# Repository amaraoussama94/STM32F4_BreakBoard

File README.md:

# STM32F4_BreakBoard
-KICad 5 Project
-MCU STM32F405RGT6
-4 layer PCB
-16MHz HSE 
-Power Regulator 
-SW For MCU
-LED For Test 
-SPI USARt I2C Bus

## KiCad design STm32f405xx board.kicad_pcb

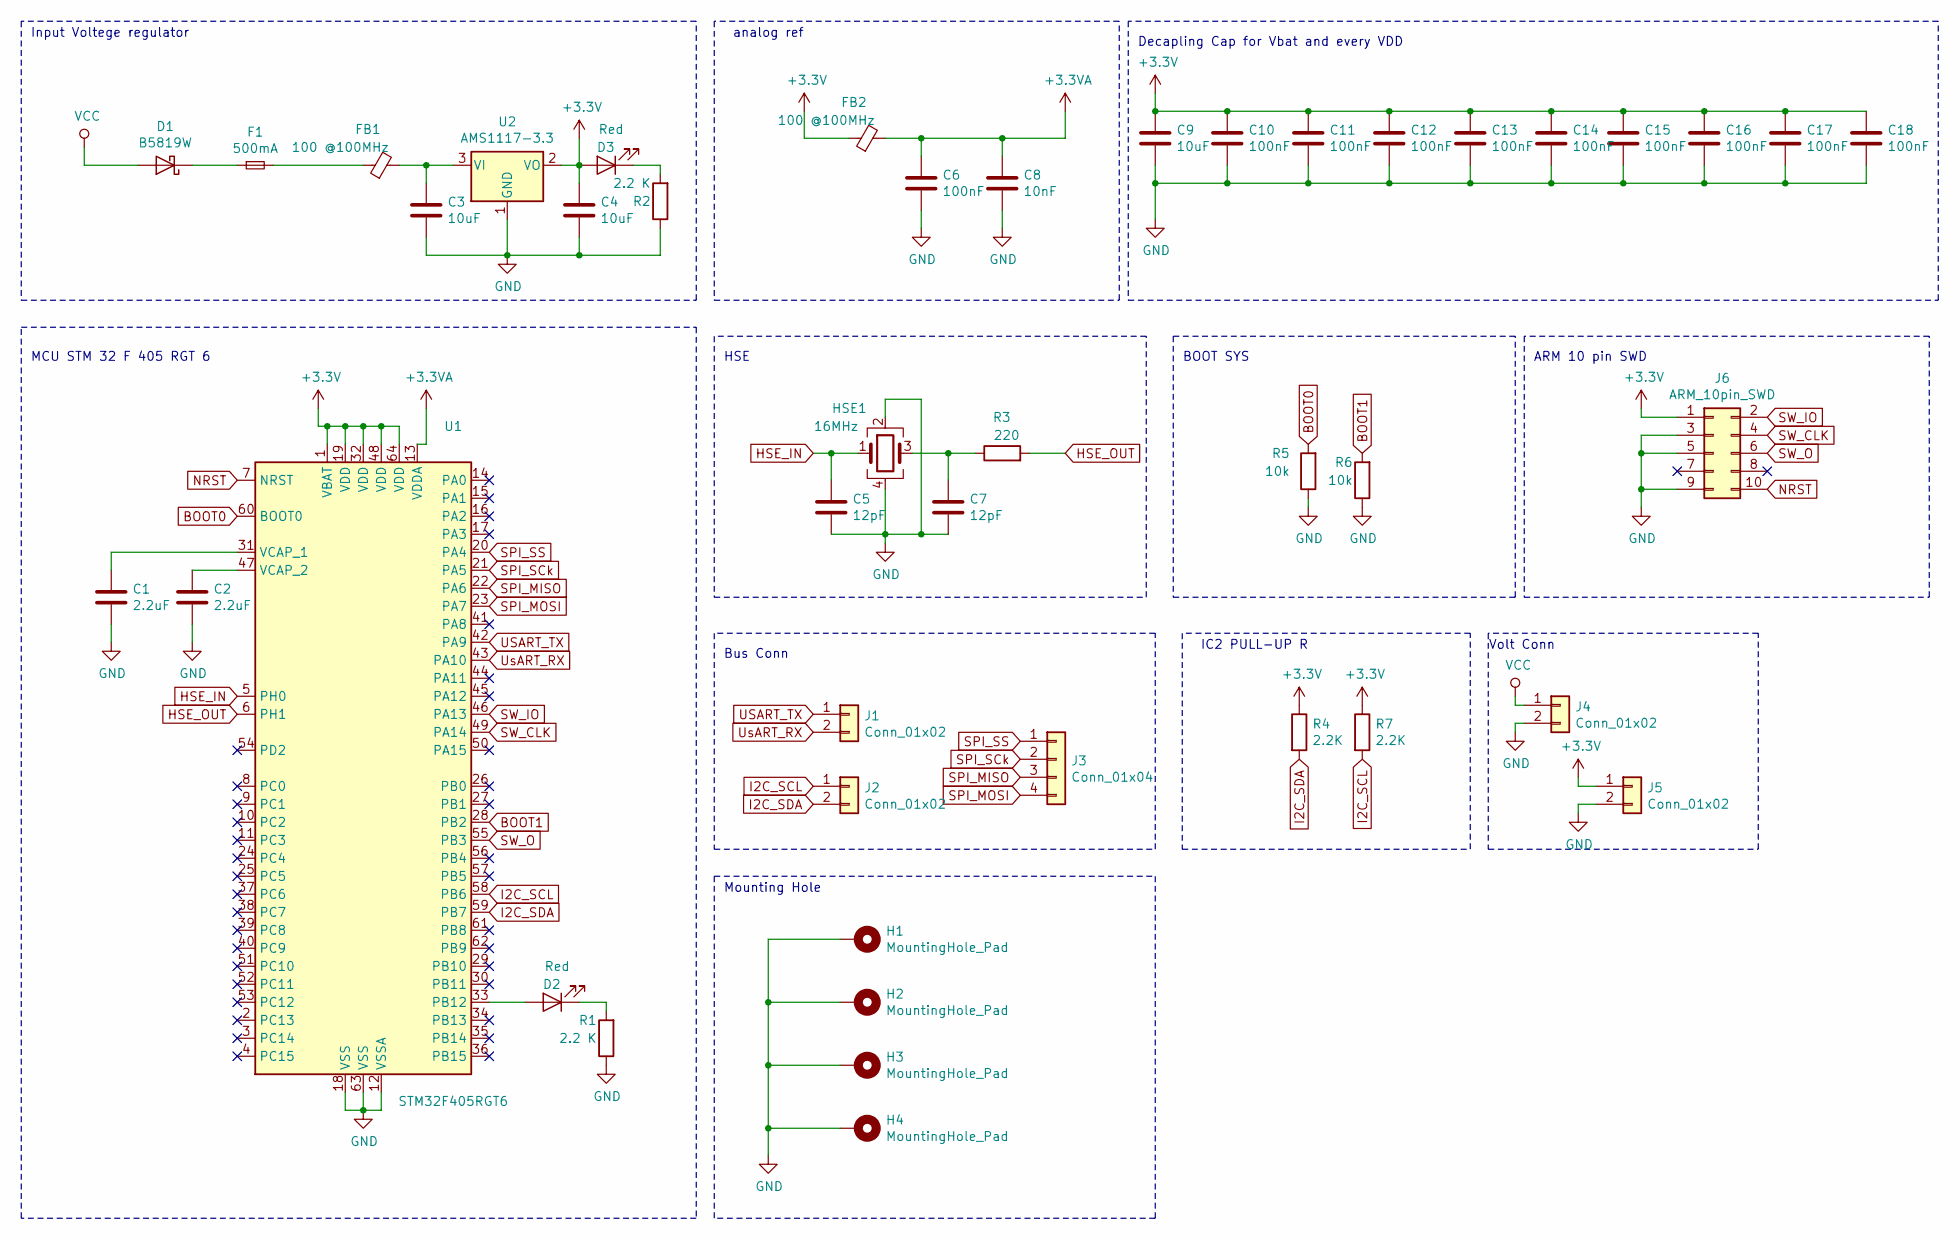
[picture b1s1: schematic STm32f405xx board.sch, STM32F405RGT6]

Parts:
C1, C2: 2.2uF; C_0603_1608Metric
C3, C4: 10uF; C_0805_2012Metric
C5, C7: 12pF; C_0402_1005Metric
C6, C10, C11, C12, C13, C14, C15, C16, C17, C18: 100nF; C_0402_1005Metric
C8: 10nF; C_0402_1005Metric
C9: 10uF; C_0603_1608Metric
D1: B5819W; D_SOD-123
D2, D3: Red; D_0603_1608Metric
F1: 500mA; Fuse_0603_1608Metric
FB1, FB2: 100 @100MHz; L_0805_2012Metric
H1, H2, H3, H4: MountingHole_Pad; MountingHole_3mm_Pad_Via
HSE1: 16MHz; Crystal_SMD_3225-4Pin_3.2x2.5mm
J1, J2, J4, J5: Conn_01x02; PinHeader_1x02_P2.54mm_Vertical
J3: Conn_01x04; PinHeader_1x04_P2.54mm_Vertical
J6: ARM_10pin_SWD; PinHeader_2x05_P1.27mm_Vertical_SMD
R1, R2: 2.2 K; R_0603_1608Metric
R3: 220; R_0402_1005Metric
R4, R7: 2.2K; R_0402_1005Metric
R5, R6: 10k; R_0402_1005Metric
U1: STM32F405RGT6; LQFP-64_10x10mm_P0.5mm
U2: AMS1117-3.3; SOT-223-3_TabPin2

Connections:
+3.3VA: C6.1, C8.1, FB2.2, U1.13 (VDDA)
+3V3: C4.1, C9.1, C10.1, C11.1, C12.1, C13.1, C14.1, C15.1, C16.1, C17.1, C18.1, D3.2 (A), FB2.1, J5.1, J6.1, R4.1, R7.1, U1.1 (VBAT), U1.19 (VDD), U1.32 (VDD), U1.48 (VDD), U1.64 (VDD), U2.2 (VO)
BOOT0: R5.2, U1.60 (BOOT0)
BOOT1: R6.2, U1.28 (PB2)
GND: C1.2, C2.2, C3.2, C4.2, C5.2, C6.2, C7.2, C8.2, C9.2, C10.2, C11.2, C12.2, C13.2, C14.2, C15.2, C16.2, C17.2, C18.2, H1.1, H2.1, H3.1, H4.1, HSE1.2, HSE1.4, J4.2, J5.2, J6.3, J6.5, J6.9, R1.1, R2.1, R5.1, R6.1, U1.12 (VSSA), U1.18 (VSS), U1.63 (VSS), U2.1 (GND)
HSE_IN: C5.1, HSE1.1, U1.5 (PH0)
HSE_OUT: R3.2, U1.6 (PH1)
I2C_SCL: J2.1, R7.2, U1.58 (PB6)
I2C_SDA: J2.2, R4.2, U1.59 (PB7)
NRST: J6.10, U1.7 (NRST)
unnamed: C1.1, U1.31 (VCAP_1)
unnamed: C2.1, U1.47 (VCAP_2)
unnamed: C3.1, FB1.2, U2.3 (VI)
unnamed: C7.1, HSE1.3, R3.1
unnamed: D1.1 (K), F1.1
unnamed: D2.1 (K), R1.2
unnamed: D2.2 (A), U1.33 (PB12)
unnamed: D3.1 (K), R2.2
unnamed: F1.2, FB1.1
SPI_MISO: J3.3, U1.22 (PA6)
SPI_MOSI: J3.4, U1.23 (PA7)
SPI_SCk: J3.2, U1.21 (PA5)
SPI_SS: J3.1, U1.20 (PA4)
SW_CLK: J6.4, U1.49 (PA14)
SW_IO: J6.2, U1.46 (PA13)
SW_O: J6.6, U1.55 (PB3)
USART_TX: J1.1, U1.42 (PA9)
UsART_RX: J1.2, U1.43 (PA10)
VCC: D1.2 (A), J4.1

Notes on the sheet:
Input Voltege regulator
analog ref
Decapling Cap for Vbat and every VDD
HSE
ARM 10 pin SWD
BOOT SYS
MCU STM 32 F 405 RGT 6
IC2 PULL-UP R
Bus Conn
Volt Conn
Mounting Hole

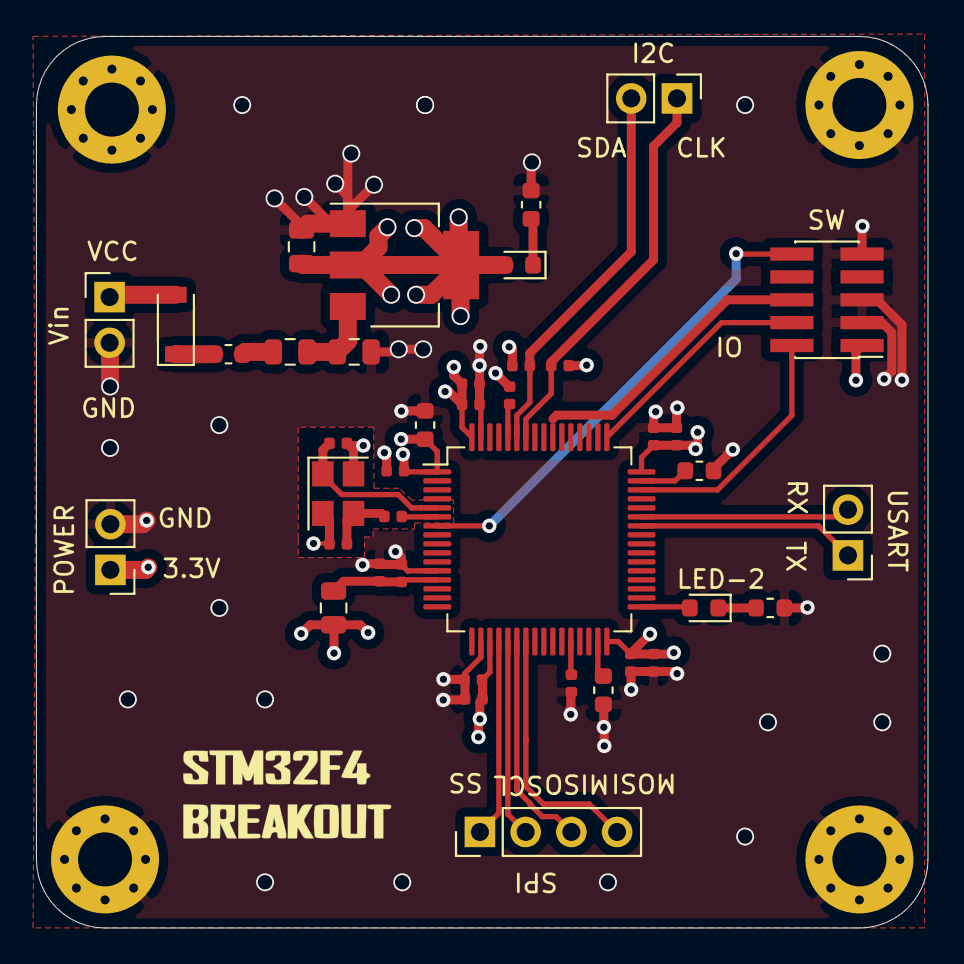
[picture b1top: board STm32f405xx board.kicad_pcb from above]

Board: 4 copper layers, 49.5 x 49.5 mm, 44 parts (0 on the bottom side), 29 nets.

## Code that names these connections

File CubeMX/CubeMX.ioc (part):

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Mcu.Name=STM32F405RGTx
Mcu.Package=LQFP64
Mcu.UserName=STM32F405RGTx
PA10.Mode=Asynchronous
PA10.Signal=USART1_RX
PA13.Mode=Trace_Asynchronous_SW
PA13.Signal=SYS_JTMS-SWDIO
PA14.Mode=Trace_Asynchronous_SW
PA14.Signal=SYS_JTCK-SWCLK
PA4.GPIOParameters=GPIO_Label
PA4.GPIO_Label=SPI1_SS
PA4.Signal=GPIO_Output
PA5.Mode=Full_Duplex_Master
PA5.Signal=SPI1_SCK
PA6.Mode=Full_Duplex_Master
PA6.Signal=SPI1_MISO
PA7.Mode=Full_Duplex_Master
PA7.Signal=SPI1_MOSI
PA9.Mode=Asynchronous
PA9.Signal=USART1_TX
PB12.GPIOParameters=GPIO_Label
PB12.GPIO_Label=LED_RED
PB12.Signal=GPIO_Output
PB3.Mode=Trace_Asynchronous_SW
PB3.Signal=SYS_JTDO-SWO
PB6.Mode=I2C
PB6.Signal=I2C1_SCL
PB7.Mode=I2C
PB7.Signal=I2C1_SDA
PH0-OSC_IN.Mode=HSE-External-Oscillator
PH0-OSC_IN.Signal=RCC_OSC_IN
PH1-OSC_OUT.Mode=HSE-External-Oscillator
PH1-OSC_OUT.Signal=RCC_OSC_OUT
RCC.HSE_VALUE=25000000
RCC.SYSCLKFreq_VALUE=16000000
board=custom
